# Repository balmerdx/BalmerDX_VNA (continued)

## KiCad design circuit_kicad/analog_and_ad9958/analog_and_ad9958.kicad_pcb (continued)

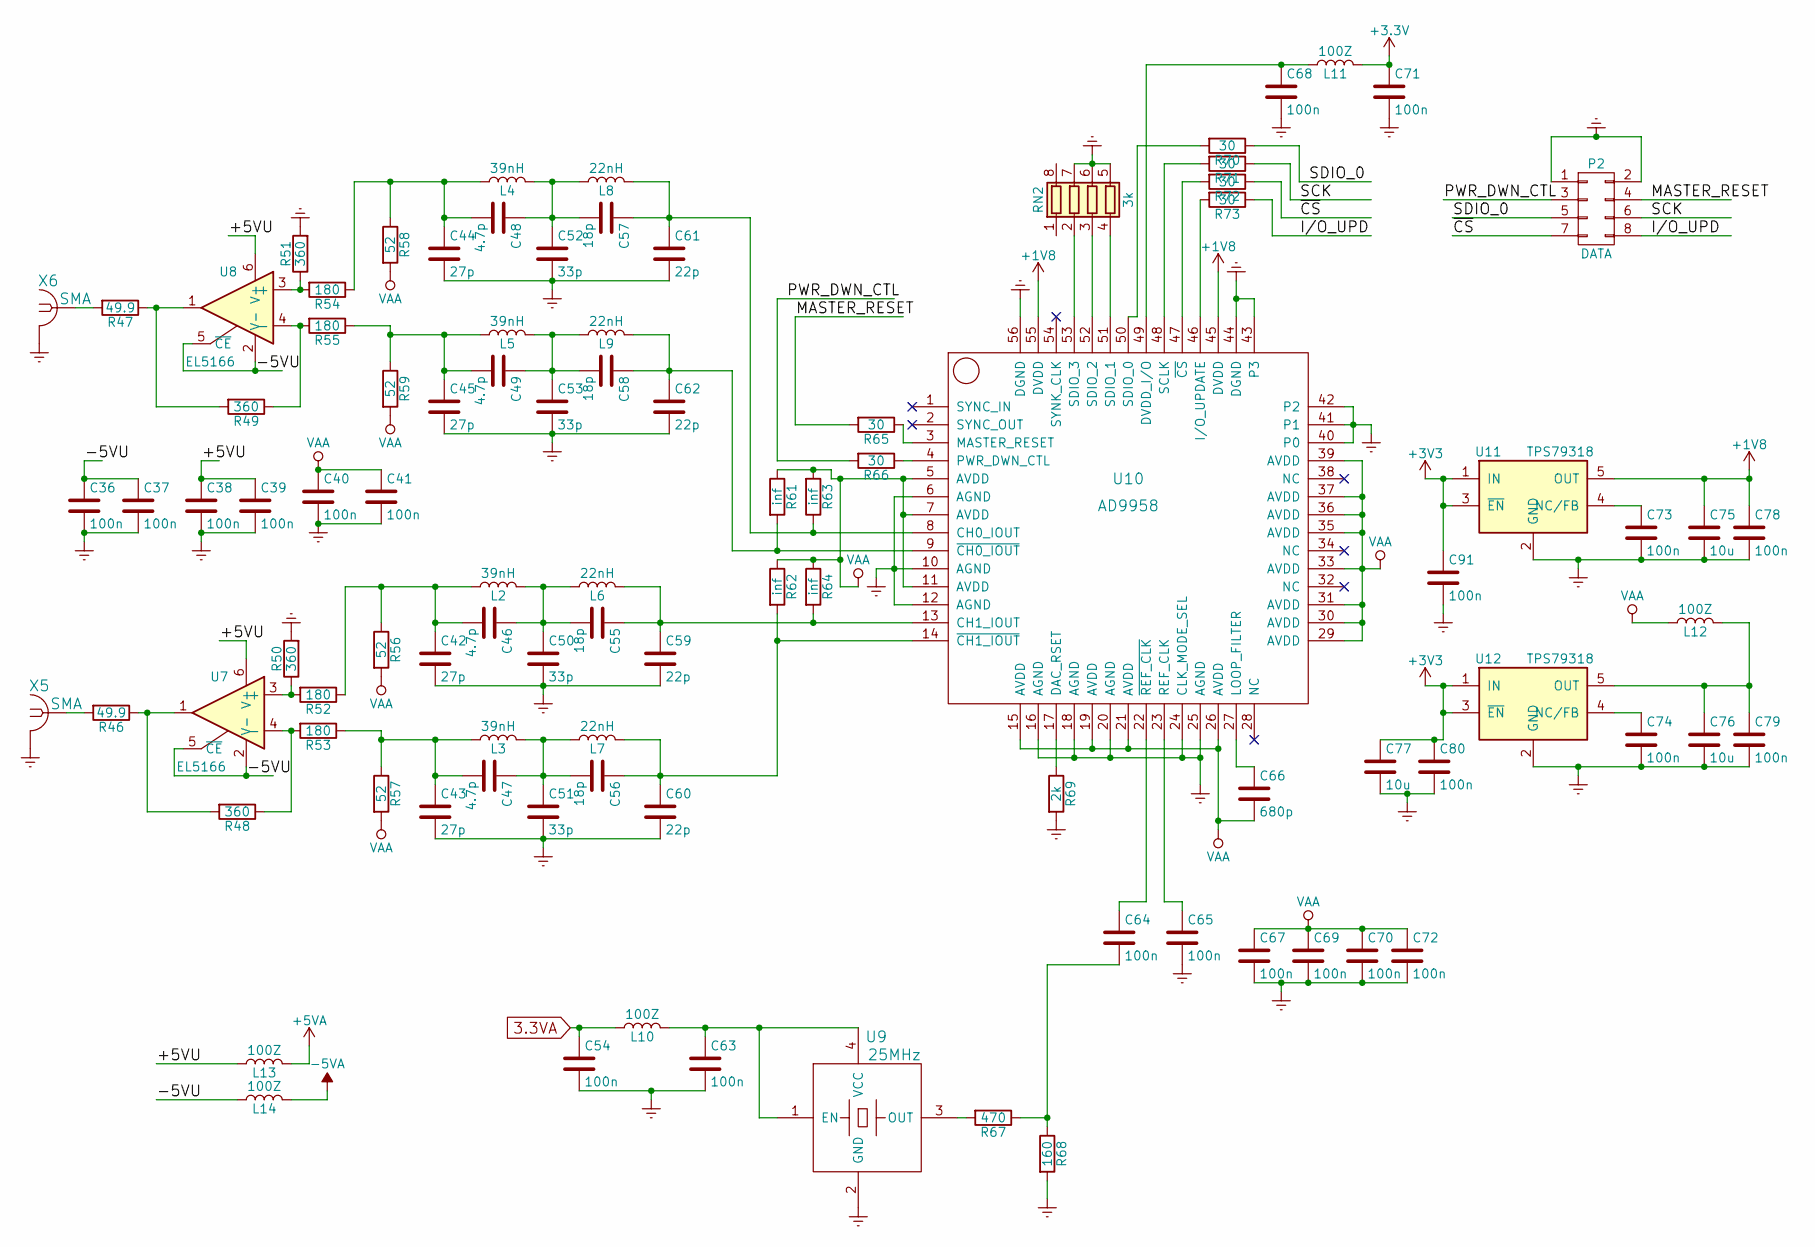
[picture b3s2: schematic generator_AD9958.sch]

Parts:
C36, C37, C38, C39, C40, C41, C54, C63, C64, C65, C67, C68, C69, C70, C71, C72, C73, C74, C78, C79, C80, C91: 100n; C_0603
C42, C43, C44, C45: 27p; R_0805
C46, C47, C48, C49: 4.7p; R_0805
C50, C51, C52, C53: 33p; R_0805
C55, C56, C57, C58: 18p; R_0805
C59, C60, C61, C62: 22p; R_0805
C66: 680p; C_0603
C75, C76, C77: 10u; C_0805
L2, L3, L4, L5: 39nH; R_0805_HandSoldering
L6, L7, L8, L9: 22nH; R_0805_HandSoldering
L10, L11, L12, L13, L14: 100Z; C_0805
P2: DATA; IDC_08M
R46, R47: 49.9; R_0603
R48, R49, R50, R51: 360; R_0603
R52, R53, R54, R55: 180; R_0603
R56, R57, R58, R59: 52; R_0603
R61, R62, R63, R64: inf; R_0603
R65, R66, R70, R71, R72, R73: 30; R_0603
R67: 470; R_0603
R68: 160; R_0603
R69: 2k; R_0603
RN2: 3k; R_Array_Concave_4x0402
U7, U8: EL5166; SOT-23-6
U9: 25MHz; Crystal_5.0x3.2mm
U10: AD9958; CP-56-1
U11, U12: TPS79318; SOT-23-5
X5, X6: SMA; SMA-NORMAL-MY

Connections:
3.3VA: C54.1, L10.1; also elsewhere on the board
+1V8: C75.1, C78.1, U10.45 (DVDD), U10.55 (DVDD), U11.5 (OUT)
+5VA: L13.2; also elsewhere on the board
-5VA: L14.2; also elsewhere on the board
/generator_AD9958/+5VU: C38.1, C39.1, L13.1, U7.6 (V+), U8.6 (V+)
/generator_AD9958/-5VU: C36.1, C37.1, L14.1, U7.2 (V-), U7.5 (~CE), U8.2 (V-), U8.5 (~CE)
/generator_AD9958/I/O_UPD: P2.8, R73.1
/generator_AD9958/MASTER_RESET: P2.4, R65.2
/generator_AD9958/PWR_DWN_CTL: P2.3, R66.2
/generator_AD9958/SCK: P2.6, R71.1
/generator_AD9958/SDIO_0: P2.5, R70.1
/generator_AD9958/~CS: P2.7, R72.1
Earth: C36.2, C37.2, C38.2, C39.2, C40.2, C41.2, C42.2, C43.2, C44.2, C45.2, C50.2, C51.2, C52.2, C53.2, C54.2, C59.2, C60.2, C61.2, C62.2, C63.2, C65.2, C67.2, C68.2, C69.2, C70.2, C71.2, C72.2, C73.2, C74.2, C75.2, C76.2, C77.2, C78.2, C79.2, C80.2, C91.2, P2.1, P2.2, R50.2, R51.2, R68.2, R69.2, RN2.5 (R4.2), RN2.6 (R3.2), RN2.7 (R2.2), U9.2 (GND), U10.6 (AGND), U10.10 (AGND), U10.12 (AGND), U10.16 (AGND), U10.18 (AGND), U10.20 (AGND), U10.24 (CLK_MODE_SEL), U10.25 (AGND), U10.40 (P0), U10.41 (P1), U10.42 (P2), U10.43 (P3), U10.44 (DGND), U10.56 (DGND), U11.2 (GND), U12.2 (GND), X5.2 (GND), X6.2 (GND); also elsewhere on the board
unnamed: C42.1, C46.2, L2.1, R52.1, R56.1
unnamed: C43.1, C47.2, L3.1, R53.1, R57.1
unnamed: C44.1, C48.2, L4.1, R54.1, R58.1
unnamed: C45.1, C49.2, L5.1, R55.1, R59.1
unnamed: C46.1, C50.1, C55.2, L2.2, L6.1
unnamed: C47.1, C51.1, C56.2, L3.2, L7.1
unnamed: C48.1, C52.1, C57.2, L4.2, L8.1
unnamed: C49.1, C53.1, C58.2, L5.2, L9.1
unnamed: C55.1, C59.1, L6.2, R64.2, U10.13 (CH1_IOUT)
unnamed: C56.1, C60.1, L7.2, R62.2, U10.14 (~CH1_IOUT)
unnamed: C57.1, C61.1, L8.2, R63.1, U10.8 (CH0_IOUT)
unnamed: C58.1, C62.1, L9.2, R61.2, U10.9 (~CH0_IOUT)
unnamed: C63.1, L10.2, U9.1 (EN), U9.4 (VCC)
unnamed: C64.1, U10.22 (~REF_CLK)
unnamed: C64.2, R67.1, R68.1
unnamed: C65.1, U10.23 (REF_CLK)
unnamed: C66.1, U10.27 (LOOP_FILTER)
unnamed: C68.1, L11.1, U10.49 (DVDD_I/O)
unnamed: C73.1, U11.4 (NC/FB)
unnamed: C74.1, U12.4 (NC/FB)
unnamed: C76.1, C79.1, L12.2, U12.5 (OUT)
unnamed: R46.1, R48.2, U7.1
unnamed: R46.2, X5.1
unnamed: R47.1, R49.2, U8.1
unnamed: R47.2, X6.1
unnamed: R48.1, R53.2, U7.4 (-)
unnamed: R49.1, R55.2, U8.4 (-)
unnamed: R50.1, R52.2, U7.3 (+)
unnamed: R51.1, R54.2, U8.3 (+)
unnamed: R65.1, U10.3 (MASTER_RESET)
unnamed: R66.1, U10.4 (PWR_DWN_CTL)
unnamed: R67.2, U9.3 (OUT)
unnamed: R69.1, U10.17 (DAC_RSET)
unnamed: R70.2, U10.50 (SDIO_0)
unnamed: R71.2, U10.48 (SCLK)
unnamed: R72.2, U10.47 (~CS)
unnamed: R73.2, U10.46 (I/O_UPDATE)
unnamed: RN2.2 (R2.1), U10.53 (SDIO_3)
unnamed: RN2.3 (R3.1), U10.52 (SDIO_2)
unnamed: RN2.4 (R4.1), U10.51 (SDIO_1)
VAA: C40.1, C41.1, C66.2, C67.1, C69.1, C70.1, C72.1, L12.1, R56.2, R57.2, R58.2, R59.2, R61.1, R62.1, R63.2, R64.1, U10.5 (AVDD), U10.7 (AVDD), U10.11 (AVDD), U10.15 (AVDD), U10.19 (AVDD), U10.21 (AVDD), U10.26 (AVDD), U10.29 (AVDD), U10.30 (AVDD), U10.31 (AVDD), U10.33 (AVDD), U10.35 (AVDD), U10.36 (AVDD), U10.37 (AVDD), U10.39 (AVDD)

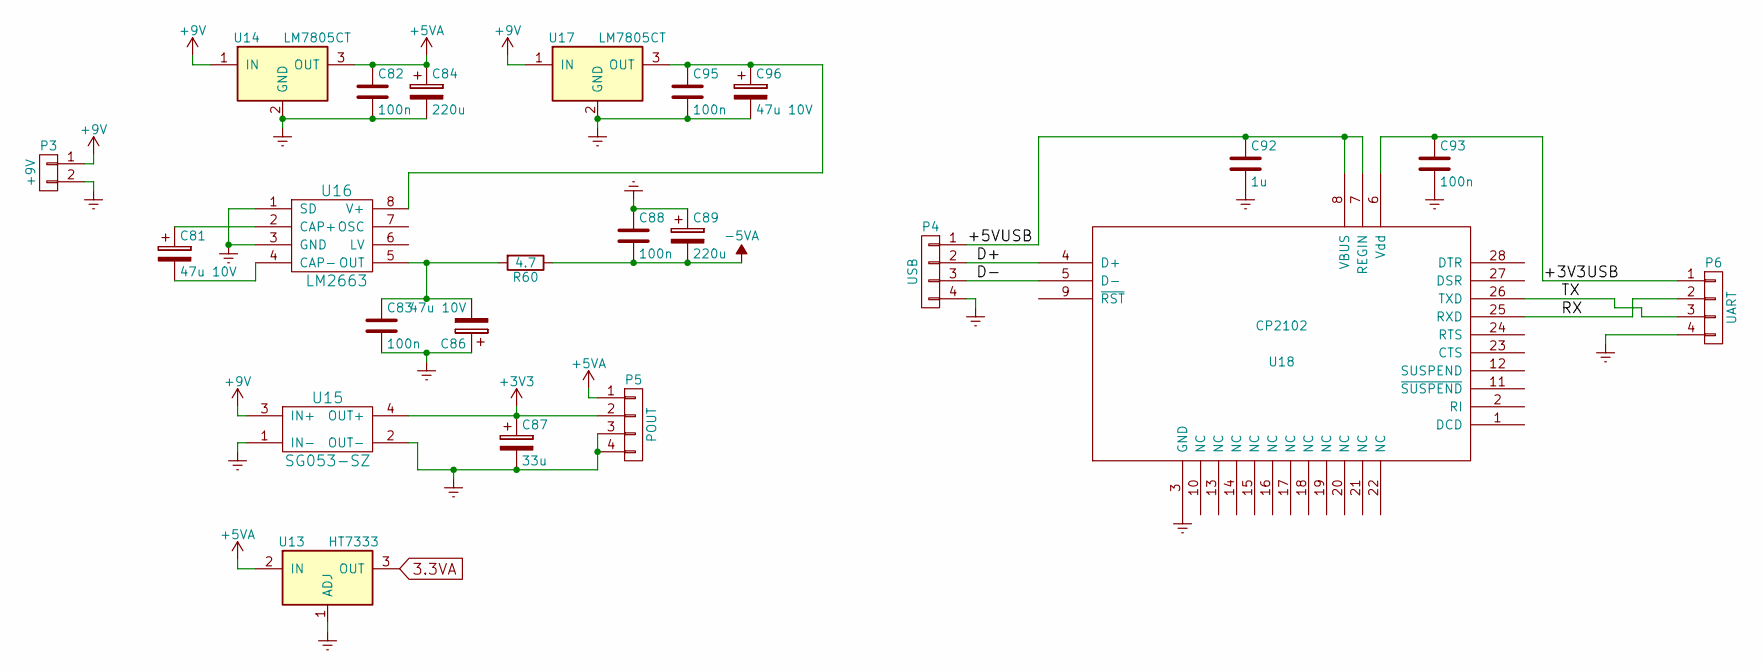
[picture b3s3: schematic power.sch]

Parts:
C81, C86, C96: 47u 10V; TantalC_SizeB_EIA-3528_HandSoldering
C82, C83, C88, C93, C95: 100n; C_0603
C84, C89: 220u; c_elec_6.3x4.5
C87: 33u; c_elec_6.3x4.5
C92: 1u; C_0603
P3: +9V; Pin_Header_Straight_1x02
P4: USB; Pin_Header_Straight_1x04
P5: POUT; Pin_Header_Straight_1x04
P6: UART; Pin_Header_Straight_1x04
R60: 4.7; R_0603
U13: HT7333; SOT89-3_Housing
U14, U17: LM7805CT; TO-220
U15: SG053-SZ
U16: LM2663; SOIC-8-N
U18: CP2102; MLP-28

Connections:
3.3VA: U13.3 (OUT); also elsewhere on the board
+5VA: C82.1, C84.1, P5.1, U13.2 (IN), U14.3 (OUT); also elsewhere on the board
+9V: P3.1, U14.1 (IN), U15.3 (IN+), U17.1 (IN)
-5VA: C88.2, C89.2, R60.1; also elsewhere on the board
/power/+3V3USB: C93.1, P6.1, U18.6 (Vdd)
/power/+5VUSB: C92.1, P4.1, U18.7 (REGIN), U18.8 (VBUS)
/power/D+: P4.2, U18.4 (D+)
/power/D-: P4.3, U18.5 (D-)
/power/RX: P6.2, U18.25 (RXD)
/power/TX: P6.3, U18.26 (TXD)
Earth: C82.2, C83.2, C84.2, C86.1, C87.2, C88.1, C89.1, C92.2, C93.2, C95.2, C96.2, P3.2, P4.4, P5.3, P5.4, P6.4, U13.1 (ADJ), U14.2 (GND), U15.1 (IN-), U15.2 (OUT-), U16.1 (SD), U16.3 (GND), U17.2 (GND), U18.3 (GND); also elsewhere on the board
unnamed: C81.1, U16.2 (CAP+)
unnamed: C81.2, U16.4 (CAP-)
unnamed: C83.1, C86.2, R60.2, U16.5 (OUT)
unnamed: C95.1, C96.1, U16.8 (V+), U17.3 (OUT)

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
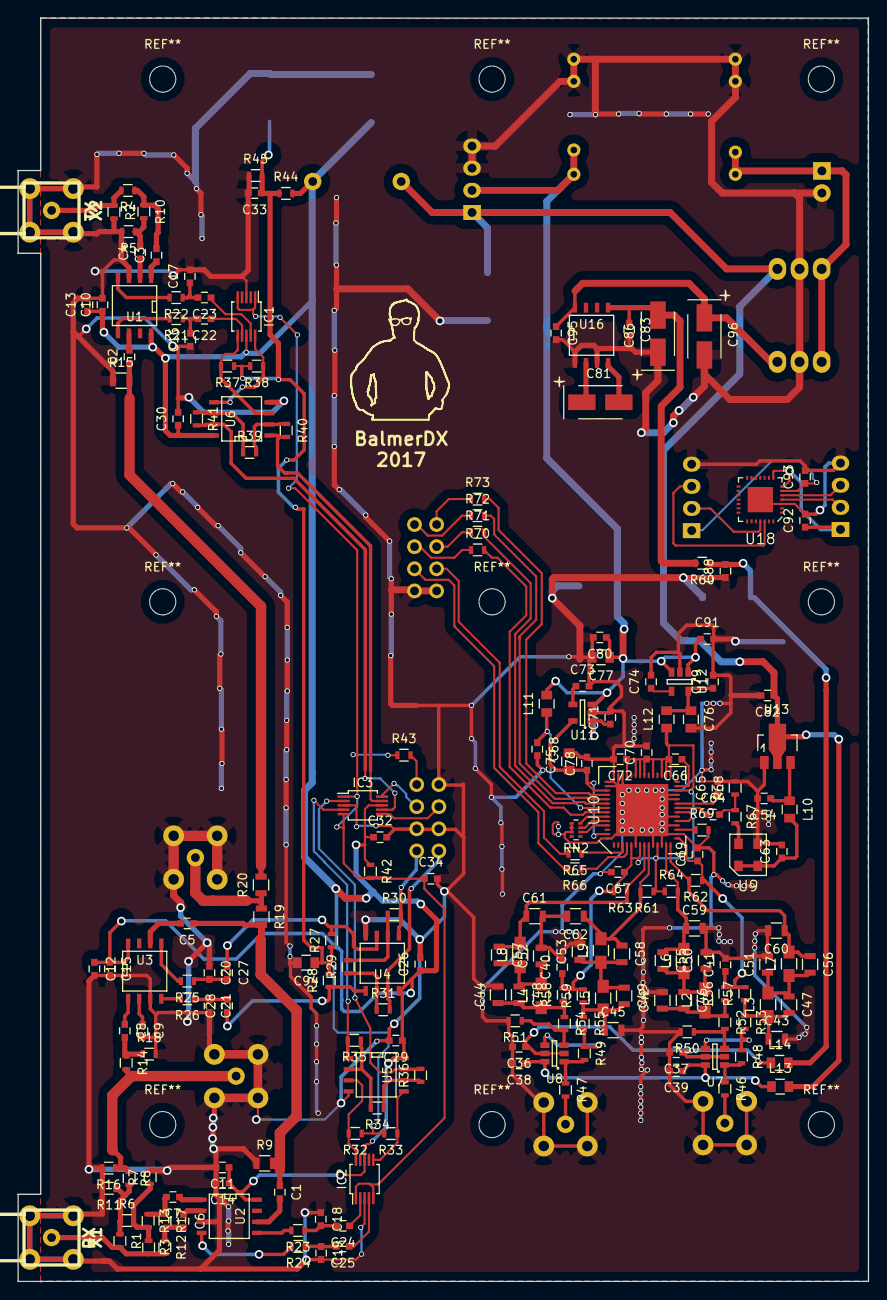
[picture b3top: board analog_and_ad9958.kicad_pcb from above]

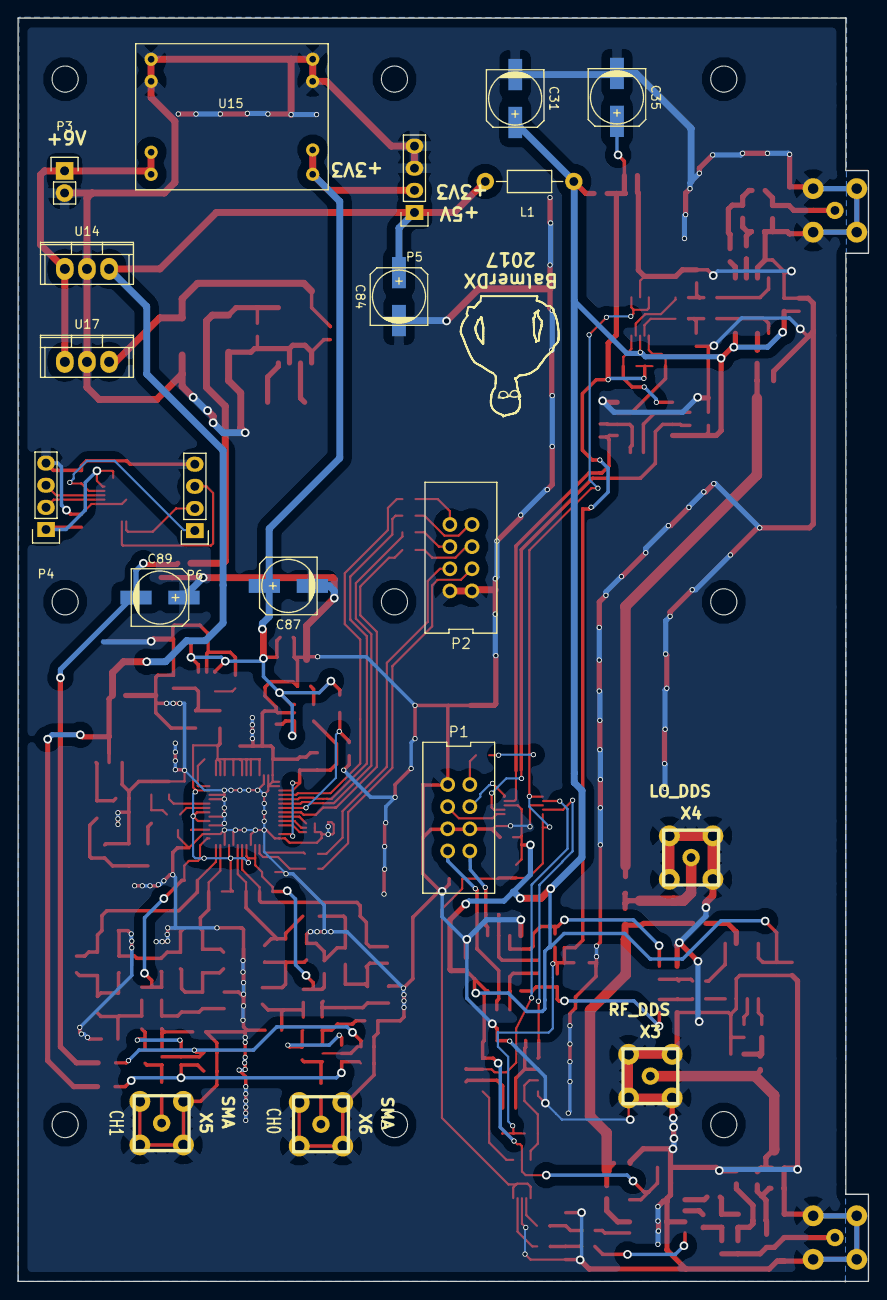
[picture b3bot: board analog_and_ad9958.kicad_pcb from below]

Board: 4 copper layers, 97.6 x 145.1 mm, 217 parts (20 on the bottom side), 128 nets.

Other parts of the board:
balmer_logo: balmer; balmer_logo
balmer_logo#2: balmer; balmer_logo

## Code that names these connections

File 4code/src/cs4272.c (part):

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#define RST_HIGH		GPIO_SetBits(GPIOB, GPIO_Pin_14)
#define RST_LOW			GPIO_ResetBits(GPIOB, GPIO_Pin_14)

//  RST - PB14

// SPI2_SCL PB10
// SPI2_SDA PB11
// SPI2_NSS PB12
// SPI2_SCK PB13
// I2S2_SD  PB15

#else

#define SOUND_DMA_STREAM DMA1_Stream0
#define SOUND_DMA_CHANNEL DMA_Channel_0

//	CCLK - PB6
//	CDIN - PB7
//  RST - PB8

// SPI3_NSS PA15
// SPI3_SCK PC10
// I2S3_SD  PC12

#define CS_I2C I2C1
#define CS_SPI SPI3
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	/* setup SCL and SDA pins
	 * You can connect I2C1 to two different
	 * pairs of pins:
	 * 1. SCL on PB6 and SDA on PB7
	 * 2. SCL on PB8 and SDA on PB9
	 */
	GPIO_InitStruct.GPIO_Pin = GPIO_Pin_6 | GPIO_Pin_7; // we are going to use PB6 and PB7
	GPIO_InitStruct.GPIO_Mode = GPIO_Mode_AF;			// set pins to alternate function
	GPIO_InitStruct.GPIO_Speed = GPIO_Speed_2MHz;//GPIO_Speed_50MHz;		// set GPIO speed
	GPIO_InitStruct.GPIO_OType = GPIO_OType_OD;			// set output to open drain --> the line has to be only pulled low, not driven high
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
#ifdef DISPLAY_ILI9481
    //I2S2 used
    //SPI3_NSS PB12
    //SPI3_SCK PB13
    //I2S3_SD  PB15
    RCC_APB1PeriphClockCmd(RCC_APB1Periph_SPI2, ENABLE);
    RCC_AHB1PeriphClockCmd(RCC_AHB1Periph_DMA1, ENABLE);
    RCC_AHB1PeriphClockCmd(RCC_AHB1Periph_GPIOB, ENABLE);
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    I2S_Init(CS_SPI, &I2S_InitStruct);
#else
    //I2S3 used
	//PA15 - NSS
	//PC10 - SCK
	//PC12 - MOSI
	RCC_APB1PeriphClockCmd(RCC_APB1Periph_SPI3, ENABLE);
	RCC_AHB1PeriphClockCmd(RCC_AHB1Periph_DMA1, ENABLE);
	RCC_AHB1PeriphClockCmd(RCC_AHB1Periph_GPIOA|RCC_AHB1Periph_GPIOC, ENABLE);
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
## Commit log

2018-08-30 Первоначальный коммит. Вся работа за пару лет.
2018-08-30 На одной из плат нестабильно запускался I2C в CS4272. Новый компилятор скомпилировал код быстрее старого.
2018-08-30 - картинки для wiki
2018-08-30 Revert "- картинки для wiki"
    This reverts commit e611a227d7c4d12c0f9eca241eb6663d6c6bd19e.
2018-08-30 - картинки нормального размера
2018-08-31 - schematic pdf
2018-08-31 - схемы в png
2018-08-31 - move files
2018-08-31 - фотки плат
2018-08-31 - забыли откадрировать
2018-09-01 - home image
2018-09-01 Revert "- home image"
    This reverts commit 3817c017e758a053aedea9e378c32dfd5d6947c4.
2018-09-01 - frontend shots
2018-09-02 - device images
2018-09-02 - SOLT calibration
2018-09-02 - StepDown MP1584
